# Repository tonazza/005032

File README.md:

View this project on [CADLAB.io](https://cadlab.io/project/25240). 

# 005032

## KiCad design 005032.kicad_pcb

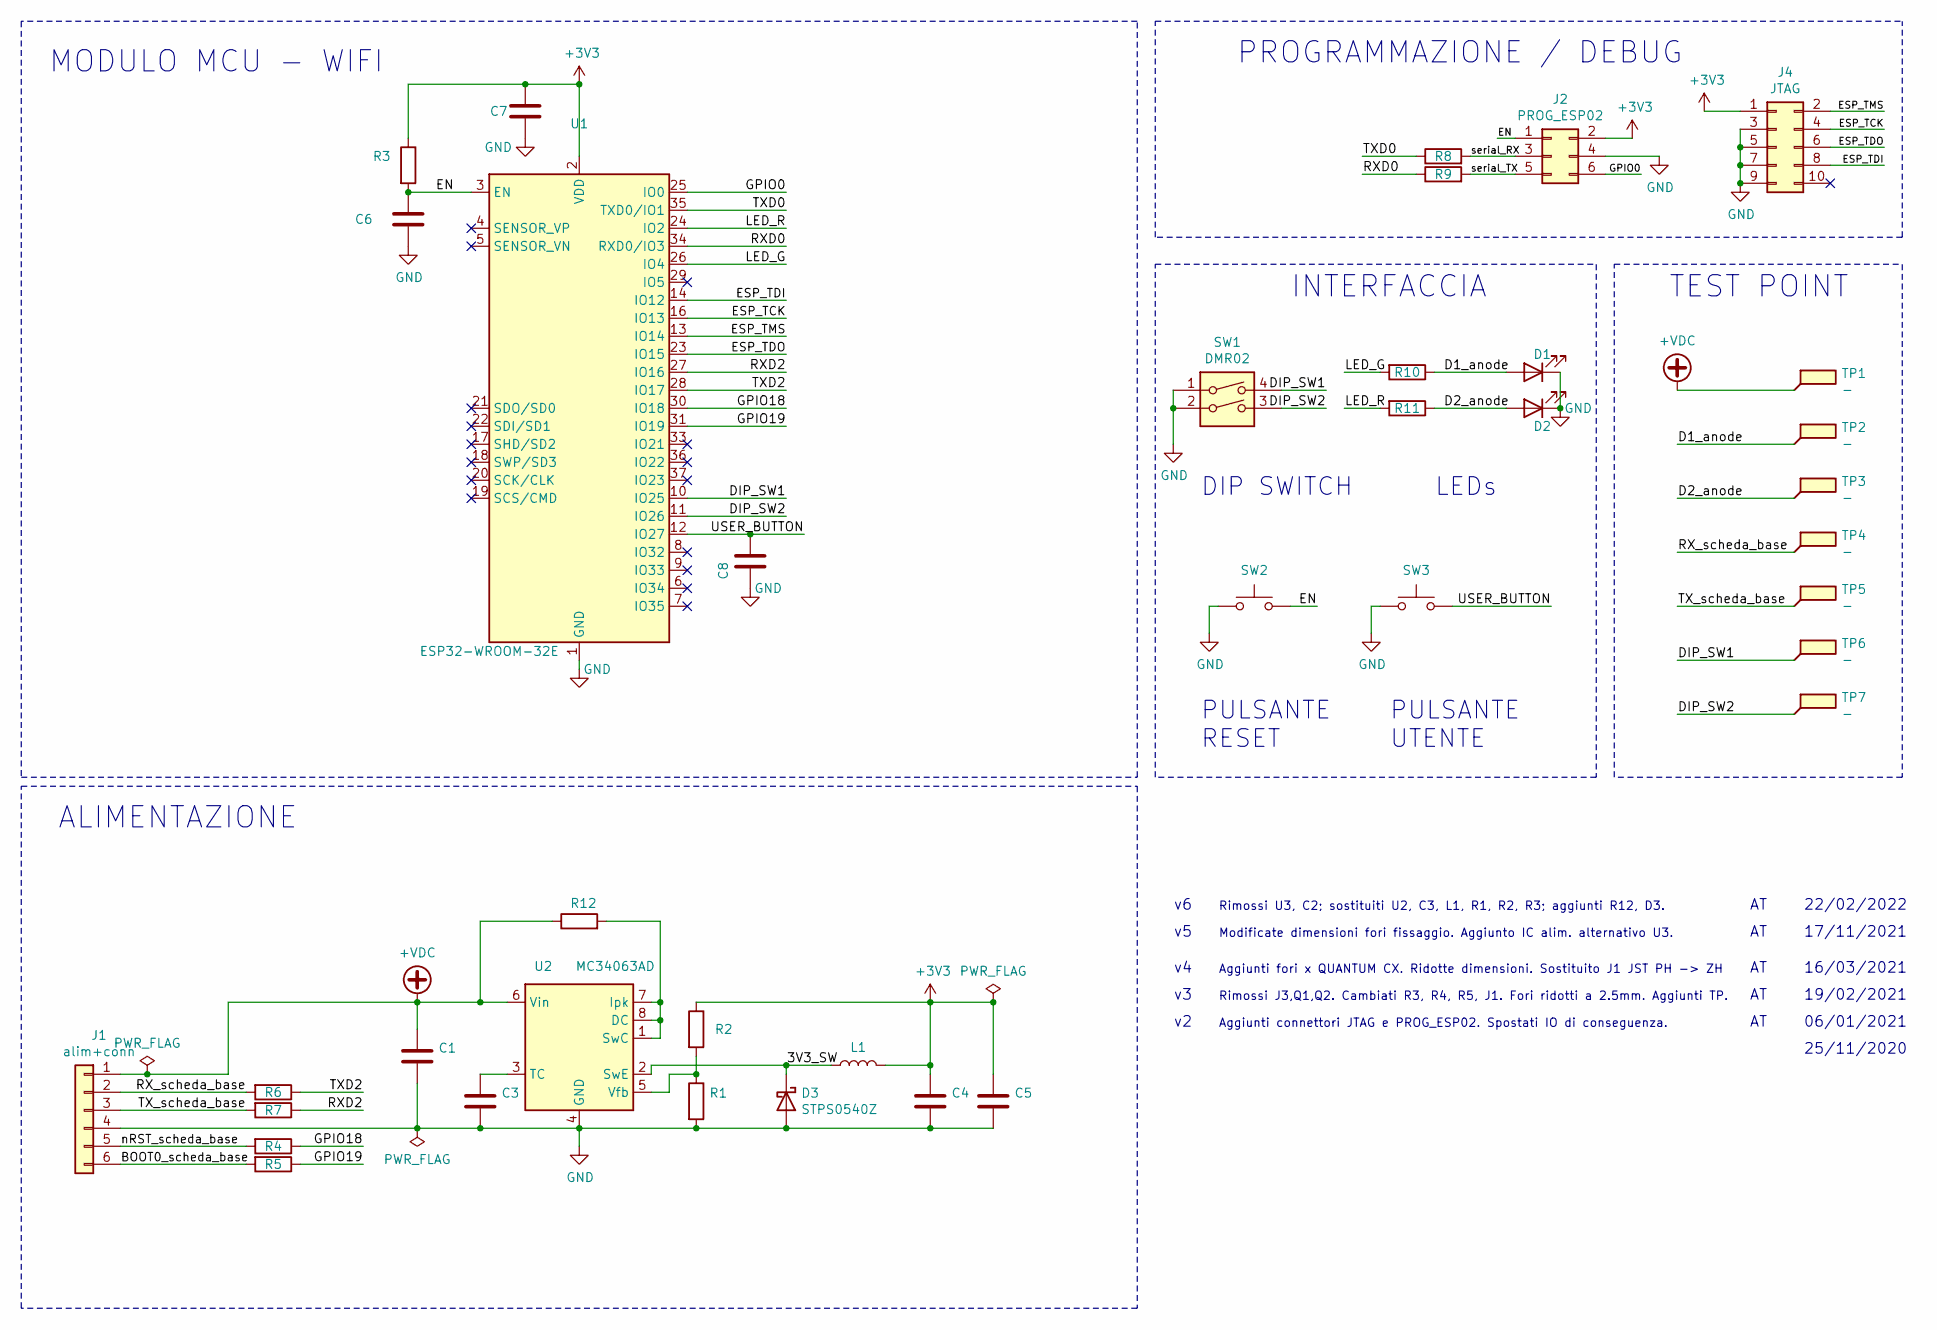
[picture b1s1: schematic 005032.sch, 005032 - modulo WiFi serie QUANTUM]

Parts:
C1: 10u/35; C_1206_3216Metric_Pad1.42x1.75mm_HandSolder
C3: 220p; C_0603_1608Metric
C4, C5: 22u/6.3; C_0805_2012Metric_Pad1.15x1.40mm_HandSolder
C6, C7, C8: 0.1u; C_0603_1608Metric
D1: 0603 green for 3.3V; LED_0603_1608Metric
D2: 0603 red for 3.3V; LED_0603_1608Metric
D3: STPS0540Z; D_SOD-123
J1: alim+conn; JST_ZH_S6B-ZR-SM4A-TF
J2: PROG_ESP02; IDC_2x03_P2.54mm_Vertical_SMD
J4: JTAG; IDC_2x05_P1.27mm_Vertical_SMD
L1: NRS5030T220MMGJ; L_Taiyo-Yuden_NR-50xx
R1: 11K 1%; R_0603_1608Metric
R2, R3: 18K 1%; R_0603_1608Metric
R4, R5, R6, R7, R8, R9, R10, R11: 100R; R_0603_1608Metric
R12: 0R33 1%; R_1206_3216Metric_Pad1.42x1.75mm_HandSolder
SW1: DMR02; SW_DIP_SPSTx02_Slide_6.7x6.64mm_W8.61mm_P2.54mm_LowProfile
SW2, SW3: 434153017835; SW_Push_1P1T_NO_3.5x2.8
TP1, TP2, TP3, TP4, TP5, TP6, TP7: -; TestPoint_round_2.0mm
U1: ESP32-WROOM-32E
U2: MC34063AD; SOIC-8_3.9x4.9mm_P1.27mm

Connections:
+3V3: C4.1, C5.1, C7.1, J2.2, J4.1, L1.2, R2.1, R3.1, U1.2 (VDD)
+VDC: C1.1, J1.1, R12.1, TP1.1, U2.6 (Vin)
/3V3_SW: D3.1 (K), L1.1, U2.2 (SwE)
/BOOT0_scheda_base: J1.6, R5.2
/D1_anode: D1.2 (A), R10.1, TP2.1
/D2_anode: D2.2 (A), R11.1, TP3.1
/DIP_SW1: SW1.4, TP6.1, U1.10 (IO25)
/DIP_SW2: SW1.3, TP7.1, U1.11 (IO26)
/EN: C6.1, J2.1, R3.2, SW2.2, U1.3 (EN)
/ESP_TCK: J4.4, U1.16 (IO13)
/ESP_TDI: J4.8, U1.14 (IO12)
/ESP_TDO: J4.6, U1.23 (IO15)
/ESP_TMS: J4.2, U1.13 (IO14)
/GPIO0: J2.6, U1.25 (IO0)
/GPIO18: R4.1, U1.30 (IO18)
/GPIO19: R5.1, U1.31 (IO19)
/LED_G: R10.2, U1.26 (IO4)
/LED_R: R11.2, U1.24 (IO2)
/RXD0: R9.1, U1.34 (RXD0/IO3)
/RXD2: R7.1, U1.27 (IO16)
/RX_scheda_base: J1.2, R6.2, TP4.1
/TXD0: R8.1, U1.35 (TXD0/IO1)
/TXD2: R6.1, U1.28 (IO17)
/TX_scheda_base: J1.3, R7.2, TP5.1
/USER_BUTTON: C8.2, SW3.2, U1.12 (IO27)
/nRST_scheda_base: J1.5, R4.2
/serial_RX: J2.3, R8.2
/serial_TX: J2.5, R9.2
GND: C1.2, C3.2, C4.2, C5.2, C6.2, C7.2, C8.1, D1.1 (K), D2.1 (K), D3.2 (A), J1.4, J2.4, J4.3, J4.5, J4.7, J4.9, R1.2, SW1.1, SW1.2, SW2.1, SW3.1, U1.1 (GND), U1.15 (GND), U1.38 (GND), U1.39 (GND), U2.4 (GND)
unnamed: C3.1, U2.3 (TC)
unnamed: R1.1, R2.2, U2.5 (Vfb)
unnamed: R12.2, U2.1 (SwC), U2.7 (Ipk), U2.8 (DC)

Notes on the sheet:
25/11/2020
PROGRAMMAZIONE / DEBUG
MODULO MCU - WIFI
ALIMENTAZIONE
INTERFACCIA
PULSANTE RESET
PULSANTE UTENTE
DIP SWITCH
LEDs
Aggiunti connettori JTAG e PROG_ESP02. Spostati IO di conseguenza.
06/01/2021
19/02/2021
Rimossi J3,Q1,Q2. Cambiati R3, R4, R5, J1. Fori ridotti a 2.5mm. Aggiunti TP.
TEST POINT
Aggiunti fori x QUANTUM CX. Ridotte dimensioni. Sostituito J1 JST PH -> ZH
16/03/2021
Modificate dimensioni fori fissaggio. Aggiunto IC alim. alternativo U3.
17/11/2021
Rimossi U3, C2; sostituiti U2, C3, L1, R1, R2, R3; aggiunti R12, D3.
22/02/2022

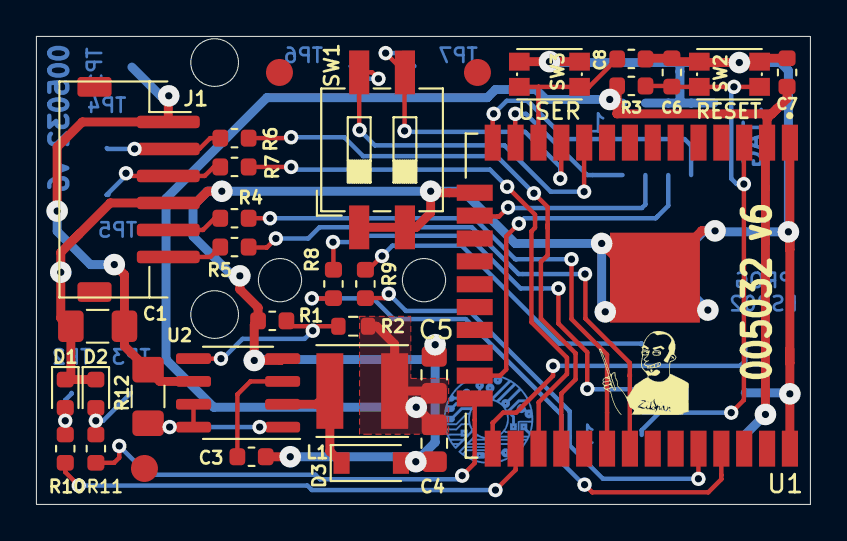
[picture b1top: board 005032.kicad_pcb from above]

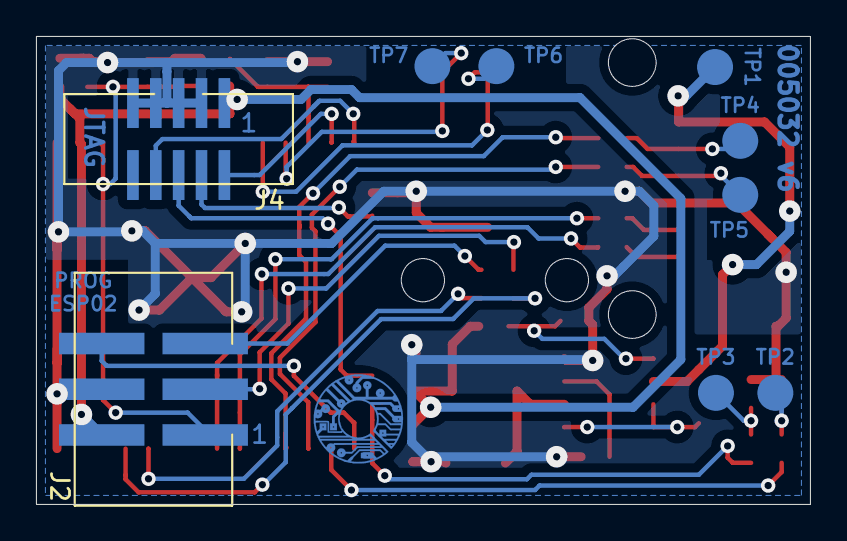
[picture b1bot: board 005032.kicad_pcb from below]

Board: 2 copper layers, 43.0 x 26.0 mm, 42 parts (9 on the bottom side), 32 nets.

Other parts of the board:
Hole2.4_1, Hole2.4_2: Hole_2.4mm
Hole2.65_1, Hole2.65_2: Hole_2.65mm

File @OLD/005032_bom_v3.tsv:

Quantity Per PCB	NOTE	Value	Footprint	Description	References	CMP_DB_AQ
4		0.1u	C_0603_1608Metric	Unpolarized capacitor	C2 C6 C7 C8	CAP00-000-005
1		10u/35	C_1206_3216Metric_Pad1.42x1.75mm_HandSolder	Unpolarized capacitor	C1	CAP00-000-037
1		220p	C_0603_1608Metric	Unpolarized capacitor	C3	CAP00-000-011
2		22u/6.3	C_0805_2012Metric_Pad1.15x1.40mm_HandSolder	Unpolarized capacitor	C4 C5	CAP00-000-034
1		0603 green for 3.3V	LED_0603_1608Metric	Light emitting diode	D1	DIO00-001-017
1		0603 red for 3.3V	LED_0603_1608Metric	Light emitting diode	D2	DIO00-001-016
1	NO MOUNT	JTAG	IDC_2x05_P1.27mm_Vertical_SMD	Generic connector, double row, 02x05, odd/even pin numbering scheme (row 1 odd numbers, row 2 even numbers), script generated (kicad-library-utils/schlib/autogen/connector/)	J4	CON00-000-065
1	NO MOUNT	PROG_ESP02	IDC_2x03_P2.54mm_Vertical_SMD	Generic connector, double row, 02x03, odd/even pin numbering scheme (row 1 odd numbers, row 2 even numbers), script generated (kicad-library-utils/schlib/autogen/connector/)	J2	CON00-000-064
1		alim+conn	JST_PH_S6B-PH-SM4-TB_Radaelli	Generic connector, single row, 01x06, script generated (kicad-library-utils/schlib/autogen/connector/)	J1	CON00-000-061
1		NRS4018T6R8‎	L_Taiyo-Yuden_NR-40xx	Inductor	L1	IND00-000-039
8		100R	R_0603_1608Metric	Resistor	R4 R5 R6 R7 R8 R9 R10 R11	RES00-000-020
1		180K 1%	R_0603_1608Metric	Resistor	R1	RES00-000-104
2		57.6K 1%	R_0603_1608Metric	Resistor	R2 R3	RES00-000-103
1		DMR02	SW_DIP_SPSTx02_Slide_6.7x6.64mm_W8.61mm_P2.54mm_LowProfile	2x DIP Switch, Single Pole Single Throw (SPST) switch, small symbol	SW1	ACC00-000-006
2		KSR231GLFS	SW_SPST_CK_RS282G05A3	Push button switch, generic, two pins	SW2 SW3	ACC00-001-007
1		AP63201	SOT-23-6		U2	ICO01-000-013
1		ESP32-WROOM-32E	ESP32-WROOM-32	RF Module, ESP32-D0WD SoC, Wi-Fi 802.11b/g/n, Bluetooth, BLE, 32-bit, 2.7-3.6V, onboard antenna, SMD	U1	ICD00-000-017





Component Groups:	17
Component Count:	30
Fitted Components:	30
Number of PCBs:	1
Total components:	30
Schematic Version:	v3
Schematic Date:	2021-02-10
PCB Variant:	['default']
BoM Date:	12/02/2021 16:52:12
Schematic Source:	T:\elettronica\DocumentazioneProgettiElettronici\005032 modulo WiFi serie QUANTUM\005032\005032.sch
KiCad Version:	Eeschema (5.1.8)-1

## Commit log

2022-02-21 Backlink to CADLAB.io has been added.
2022-02-21 v5 - primo commit
2022-02-22 v5 - commit prima di esecuzione modifiche v6
2022-02-22 v6 - modificato schema (PCB ancora in v5)
2022-02-22 v6 - modificato PCB (TEMP - in attesa revisione meccanica per montaggio su QUANTUM EX 100/150)
